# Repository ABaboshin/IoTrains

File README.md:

# IoTrains

Internet of Trains :)

The existing systems in the market are either with old roots (DCC) or not opensource (Märklin). More then that they were built over 20 years ago and therefore have historical restrictions. In order to be able more flexible I started to write a firmware for the trains and accessories using ESP32/ESP8266.

The projects consists of:
 - [Firmware](./firmware/) which is written in c++ using PlatformIO,
 - MQTT Broker, see [emqx](./emqx) as an example,
 - A [backend](./webui/server) written in typesript,
 - as well [frontend](./webui/client/) in react,
 - [json schema](./jsonschema/) describes a mqtt based protocol.

# License
The source code and schematic are licensed under MIT license.

The train's STL files are licensed under CC BY-NC-SA 4.0.

# Notes
 - Connect an audio amplifier to an i2s capable pin i.e. DAC_1.

## TODO
 - multiple rfid
 - responsive ui / refresh on update
 - process rfid events
 - sqlite3
 - main board max 4 x 2.3 c

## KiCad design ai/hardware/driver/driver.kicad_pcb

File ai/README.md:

# IoTrains train controller hardware (AI-generated)

Two 23 x 40 mm, 2-layer KiCad 10 boards for controlling a model train from an ESP32, joined by a 10-wire cable.

**Status:** schematics and PCBs are complete and fully routed, but nothing has been built or reviewed by a person. Routing is autorouted (Freerouting) except the buck converter, which is laid out by hand. Review both boards in KiCad before ordering.

| Board | Project | Contents |
|---|---|---|
| MCU | [hardware/mcu/mcu.kicad_pro](hardware/mcu/mcu.kicad_pro) | ESP32-S3-MINI-1-N8, MAX98357A I2S amplifier, BOOT and RESET buttons |
| Driver | [hardware/driver/driver.kicad_pro](hardware/driver/driver.kicad_pro) | Bridge rectifier, 3.3 V buck converter, BDR6133 motor driver, TLC5940 LED driver |

All parts are on the top side. Connector labels are on the bottom silkscreen. There are no mounting holes.

Every connector sits on a short edge, so all cables leave along the length of the board:

| Board | Top edge | Bottom edge (left to right) |
|---|---|---|
| MCU | Antenna, no connectors | `LINK`, `USB`, `SPK` |
| Driver | `LINK`, `3V3` | `12V`, `LED`, `MOTOR` |

## Requirements and how they are met

| Requirement | Result |
|---|---|
| Max 23 x 40 mm, up to 3 boards | 2 boards, each 23 x 40 mm |
| ESP32, module or bare chip, whichever is cheaper | ESP32-S3-MINI-1-N8 module (see below) |
| S2B-ZR and SM10B-SRSS-TB connectors | Used for every connector |
| Cables must run parallel to the long side | Every connector is on a short edge |
| 12 V DC input, unknown polarity | ABS210 bridge rectifier on the input |
| USB pins on an S2B connector | `USB` on the MCU board (IO19/IO20) |
| One BDR6133 motor driver, outputs exposed | On the driver board, `MOTOR` connector |
| 6 LED outputs, TLC5940 allowed | TLC5940 with 8 outputs on the `LED` connector |
| Audio chip with speaker output, otherwise expose I2S | MAX98357A with `SPK` connector; I2S is not exposed |

**Module vs bare chip:** at JLCPCB on 2026-11-27 the module was $4.72 and the bare ESP32-S3FN8 $3.27. The $1.45 difference does not cover a crystal, RF matching parts and an antenna that needs tuning, so the module is used.

## Connectors

### MCU board

| Connector | Type | Pins |
|---|---|---|
| `LINK` (J1) | SM10B | See link pinout below |
| `USB` (J2) | S2B | 1 = D+ (IO20), 2 = D- (IO19) |
| `SPK` (J4) | S2B | 1 = SPK+, 2 = SPK- |

The MCU board has no power connector of its own. It gets 3.3 V over `LINK` pin 2.

### Driver board

| Connector | Type | Pins |
|---|---|---|
| `12V` (J1) | S2B | 12 V DC, either polarity |
| `MOTOR` (J2) | S2B | 1 = OUTA, 2 = OUTB |
| `LINK` (J3) | SM10B | See link pinout below |
| `LED` (J4) | SM10B | 1 and 10 = LED anodes (bridge output, about 10 V), 2-9 = OUT0-OUT7 |
| `3V3` (J5) | S2B | 1 = GND, 2 = +3V3 |

### Link cable

The cable must be wired 1:1 (pin n to pin n).

| Pin | Signal | ESP32 pin | Driver board |
|---|---|---|---|
| 1 | GND | | |
| 2 | +3V3 | | From the buck converter |
| 3 | GSCLK | IO11 | TLC5940 |
| 4 | BLANK | IO12 | TLC5940, 10k pull-up |
| 5 | SIN | IO13 | TLC5940 |
| 6 | SCLK | IO14 | TLC5940 |
| 7 | XLAT | IO15 | TLC5940 |
| 8 | VPRG | IO16 | TLC5940, 10k pull-down |
| 9 | MOT_A | IO17 | BDR6133 INA, 100k pull-down |
| 10 | MOT_B | IO18 | BDR6133 INB, 100k pull-down |

The TLC5940 pins match the mapping in the comment in `firmware/basic_train/src/main.cpp`.

## Circuit notes

### Power

- The 12 V input goes through the ABS210 bridge, so polarity does not matter. The bridge output (`VM`, about 10 V) feeds the motor driver, the LED anodes and the buck converter.
- A TPS629210 makes 3.3 V. It is configured the same way as the existing `hardware/tps6292` board: 249k on VSET (3.3 V) and 52.3k on S-CONF (2.5 MHz, forced PWM, output discharge off).
- Keep the input at 16 V or below. The buck converter and the TLC5940 outputs are rated to 17 V.
- The S2B connectors are rated 1 A, which limits motor current.
- The `3V3` connector on the driver board is for powering both boards without 12 V, for example from a USB adapter while flashing. Do not feed 3.3 V into it while 12 V is connected.

### Motor

- BDR6133 logic: INA high / INB low = forward, INA low / INB high = reverse, both high = brake, both low = stop.
- The pull-downs keep the motor off while the ESP32 boots.

### LEDs

- Each output is a constant-current sink of 8.3 mA (39.06 / 4.7k), so LEDs need no series resistors. Connect each LED between an anode pin and an output pin.
- BLANK is pulled high so the LEDs stay off until the firmware runs.
- DCPRG is tied to 3.3 V, as on the existing `hardware/tlc5940` board. The dot-correction register is undefined after power-up, so the firmware must write it (with VPRG high) before using the outputs.
- OUT8-OUT15 are not connected.

### Audio

| Signal | ESP32 pin |
|---|---|
| I2S DIN | IO47 |
| I2S BCLK | IO33 |
| I2S LRCLK | IO34 |
| Amplifier SD_MODE | IO21, 510k pull-up to 3.3 V |

- With IO21 floating, the amplifier plays (L+R)/2. Driving IO21 low shuts it down; driving it high selects the left channel only.
- Gain is fixed at 9 dB.
- The amplifier runs from 3.3 V. Expect roughly 0.6 W into 8 ohm; this is extrapolated from the datasheet's 0.77 W at 3.7 V.
- Use a 4-8 ohm speaker. The output is bridge-tied, so neither speaker wire may be connected to GND.
- The existing firmware does not drive these pins yet (the I2S code in `MP3Player.cpp` is commented out).

### ESP32

- BOOT button on IO0 (left of the module), RESET button on EN (right of the module).
- No copper is placed under the module's antenna (top 5.3 mm of the board).

## Bill of materials

Every part carries an `LCSC` field in the schematic and on the PCB footprint.

### MCU board

| Ref | Part | Package | LCSC |
|---|---|---|---|
| U1 | ESP32-S3-MINI-1-N8 | Module | C2913206 |
| U2 | MAX98357AETE+T | TQFN-16 | C910544 |
| SW1, SW2 | TS-1088 tactile switch | SMD | C720477 |
| R1 | 10k | 0402 | C25744 |
| R2 | 510k | 0402 | C11616 |
| C1, C4 | 10 uF | 0603 | C19702 |
| C2, C5 | 100 nF | 0402 | C1525 |
| C3 | 1 uF | 0402 | C52923 |
| J1 | SM10B-SRSS-TB | | C160409 |
| J2, J4 | S2B-ZR | | C157930 |

### Driver board

| Ref | Part | Package | LCSC |
|---|---|---|---|
| D1 | ABS210 bridge | ABS | C84159 |
| U1 | TPS629210DRLR | SOT-583 | C5219301 |
| U2 | BDR6133 | ESOP-8 | C2687793 |
| U3 | TLC5940PWPR | HTSSOP-28 | C181653 |
| L1 | 2.2 uH, 3.3 A | 1210 | C6021483 |
| C1, C2 | 10 uF 25 V | 0805 | C15850 |
| C3 | 22 uF | 0805 | C45783 |
| C4, C5 | 100 nF | 0402 | C1525 |
| R1 | 249k | 0603 | C22918 |
| R2 | 52.3k | 0603 | C23198 |
| R3, R4 | 100k | 0402 | C25741 |
| R5 | 4.7k | 0402 | C25900 |
| R6, R7 | 10k | 0402 | C25744 |
| J1, J2, J5 | S2B-ZR | | C157930 |
| J3, J4 | SM10B-SRSS-TB | | C160409 |

## Verification

Checked with `kicad-cli` (KiCad 10.0.1):

| Board | ERC | DRC | Unconnected | Schematic parity |
|---|---|---|---|---|
| MCU | 1 warning | 1 error, 10 warnings | 0 | OK |
| Driver | 0 | 8 warnings | 0 | OK |

- The MCU ERC warning is a pin-type mismatch on the exposed pad of the stock MAX98357A symbol.
- The MCU DRC error is a courtyard overlap between `USB` (J2) and `SPK` (J4). It is expected: the three connectors only fit on the 23 mm edge with their bodies about 0.2 mm apart.
- All DRC warnings are silkscreen overlaps between neighbouring connectors, for the same reason.
- IC pinouts were checked against the datasheets for the BDR6133, TPS629210, TLC5940 and MAX98357A.
- Design rules: 0.2 mm tracks (0.3-0.6 mm for power, motor and speaker), 0.15 mm clearance, 0.6 / 0.3 mm vias, 0.3 mm copper-to-edge.

## Before ordering

- **TLC5940PWPR (C181653):** JLCPCB showed 1 in stock on 2026-11-27, so it would be a pre-order.
- **ESP32 module:** JLCPCB lists it as "Standard PCBA only", not Economic.
- **100 nF capacitor (C1525):** LCSC's own site showed 0 stock on 2026-11-27. JLCPCB's assembly stock for it was not checked.
- **Production files:** gerbers, BOM and placement files have not been generated. Use the Fabrication Toolkit plugin as on the other boards in `hardware/`.
- **Connector spacing:** neighbouring connectors are 0.2-0.25 mm apart, and the outer ones on the bottom edges are 0.2-0.25 mm from the board edge. Check this against real parts before ordering in quantity.
- **LED tracks:** on the driver board the eight LED tracks run under the body of the bridge rectifier, between its pads.
- **Review:** look over the autorouted tracks, especially the motor and power paths.

## Regenerating the design

The KiCad files are generated from [hardware/tools/design.py](hardware/tools/design.py), which holds the parts, nets and placement for both boards.

```
python ai/hardware/tools/build.py            # both boards
python ai/hardware/tools/build.py driver     # one board
```

This rewrites the schematic and PCB, re-runs the autorouter and prints the ERC/DRC summary. Manual edits made in KiCad are lost, and the routing differs on every run.

It needs:

- KiCad 10 in `C:\Program Files\KiCad\10.0`
- Java 21 and `freerouting-1.9.0.jar` in `%TEMP%` (from the Freerouting GitHub releases; 2.1.0 failed to route these boards)
- The JST footprint libraries `LIB_S2B-ZR_LF__SN_` and `LIB_SM10B-SRSS-TB_LF__SN_` in KiCad's global footprint table
- `hardware/esp32/esp32.kicad_pro` in this repo, used as the project template

| File | Purpose |
|---|---|
| `design.py` | Parts, nets, schematic and PCB positions, hand-routed tracks |
| `gen_sch.py` | Writes the schematic, project file and library tables |
| `gen_pcb.py` | Places footprints, autoroutes, adds ground pours and labels |
| `check.py` | Runs ERC and DRC and prints a summary |
| `build.py` | Runs the three steps above |
| `build_lib.py` | Rebuilds `hardware/lib` from symbols and footprints in the repo's existing boards |
| `sexp.py`, `symlib.py`, `netlist.py` | Helpers for KiCad file formats |

The shared symbols and footprints are in [hardware/lib](hardware/lib).

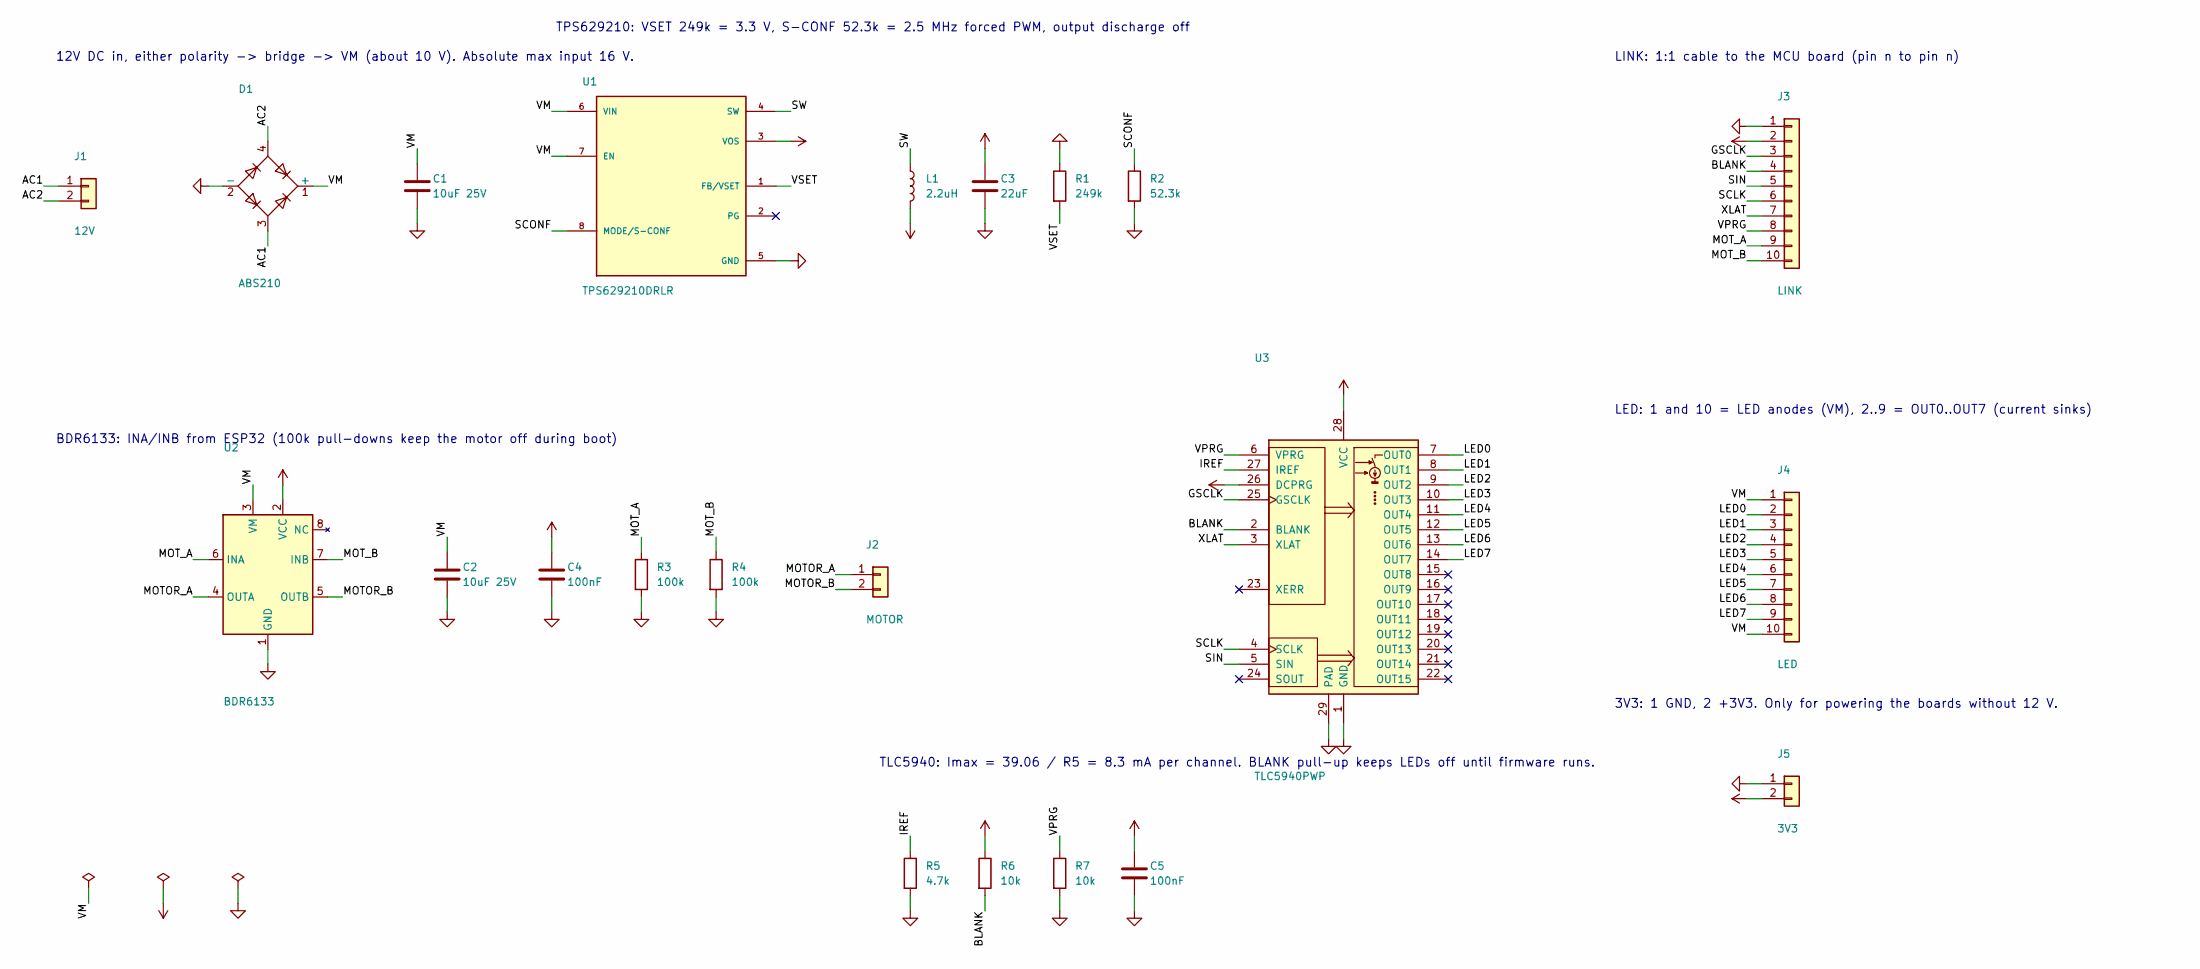
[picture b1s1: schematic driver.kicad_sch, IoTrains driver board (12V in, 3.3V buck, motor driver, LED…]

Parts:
C1, C2: 10uF 25V; C_0805_2012Metric; LCSC C15850
C3: 22uF; C_0805_2012Metric; LCSC C45783
C4, C5: 100nF; C_0402_1005Metric; LCSC C1525
D1: ABS210; Diode_Bridge_Diotec_ABS; LCSC C84159
J1: 12V; S2BZRLFSN; LCSC C157930
J2: MOTOR; S2BZRLFSN; LCSC C157930
J3: LINK; SM10B-SRSS-TB; LCSC C160409
J4: LED; SM10B-SRSS-TB; LCSC C160409
J5: 3V3; S2BZRLFSN; LCSC C157930
L1: 2.2uH; L_1210_3225Metric; LCSC C6021483
R1: 249k; R_0603_1608Metric; LCSC C22918
R2: 52.3k; R_0603_1608Metric; LCSC C23198
R3, R4: 100k; R_0402_1005Metric; LCSC C25741
R5: 4.7k; R_0402_1005Metric; LCSC C25900
R6, R7: 10k; R_0402_1005Metric; LCSC C25744
U1: TPS629210DRLR; SOT-583-8; LCSC C5219301
U2: BDR6133; SOIC-8-1EP_3.9x4.9mm_P1.27mm_EP2.41x3.3mm_ThermalVias; LCSC C2687793
U3: TLC5940PWP; HTSSOP-28-1EP_4.4x9.7mm_P0.65mm_EP3.4x9.5mm_Mask2.4x6.17mm_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; LCSC C181653

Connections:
+3V3: C3.1, C4.1, C5.1, J3.2, J5.2, L1.2, R6.1, U1.3 (VOS), U2.2 (VCC), U3.26 (DCPRG), U3.28 (VCC)
/AC1: D1.3, J1.1
/AC2: D1.4, J1.2
/BLANK: J3.4, R6.2, U3.2 (BLANK)
/GSCLK: J3.3, U3.25 (GSCLK)
/IREF: R5.1, U3.27 (IREF)
/LED0: J4.2, U3.7 (OUT0)
/LED1: J4.3, U3.8 (OUT1)
/LED2: J4.4, U3.9 (OUT2)
/LED3: J4.5, U3.10 (OUT3)
/LED4: J4.6, U3.11 (OUT4)
/LED5: J4.7, U3.12 (OUT5)
/LED6: J4.8, U3.13 (OUT6)
/LED7: J4.9, U3.14 (OUT7)
/MOTOR_A: J2.1, U2.4 (OUTA)
/MOTOR_B: J2.2, U2.5 (OUTB)
/MOT_A: J3.9, R3.1, U2.6 (INA)
/MOT_B: J3.10, R4.1, U2.7 (INB)
/SCLK: J3.6, U3.4 (SCLK)
/SCONF: R2.1, U1.8 (MODE/S-CONF)
/SIN: J3.5, U3.5 (SIN)
/SW: L1.1, U1.4 (SW)
/VM: C1.1, C2.1, D1.1 (+), J4.1, J4.10, U1.6 (VIN), U1.7 (EN), U2.3 (VM)
/VPRG: J3.8, R7.1, U3.6 (VPRG)
/VSET: R1.2, U1.1 (FB/VSET)
/XLAT: J3.7, U3.3 (XLAT)
GND: C1.2, C2.2, C3.2, C4.2, C5.2, D1.2 (-), J3.1, J5.1, R1.1, R2.2, R3.2, R4.2, R5.2, R7.2, U1.5 (GND), U2.1 (GND), U2.9 (GND), U3.1 (GND), U3.29 (PAD)

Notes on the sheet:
12V DC in, either polarity -> bridge -> VM (about 10 V). Absolute max input 16 V.
LED: 1 and 10 = LED anodes (VM), 2..9 = OUT0..OUT7 (current sinks)
LINK: 1:1 cable to the MCU board (pin n to pin n)
3V3: 1 GND, 2 +3V3. Only for powering the boards without 12 V.
BDR6133: INA/INB from ESP32 (100k pull-downs keep the motor off during boot)
TPS629210: VSET 249k = 3.3 V, S-CONF 52.3k = 2.5 MHz forced PWM, output discharge off
TLC5940: Imax = 39.06 / R5 = 8.3 mA per channel. BLANK pull-up keeps LEDs off until firmware runs.

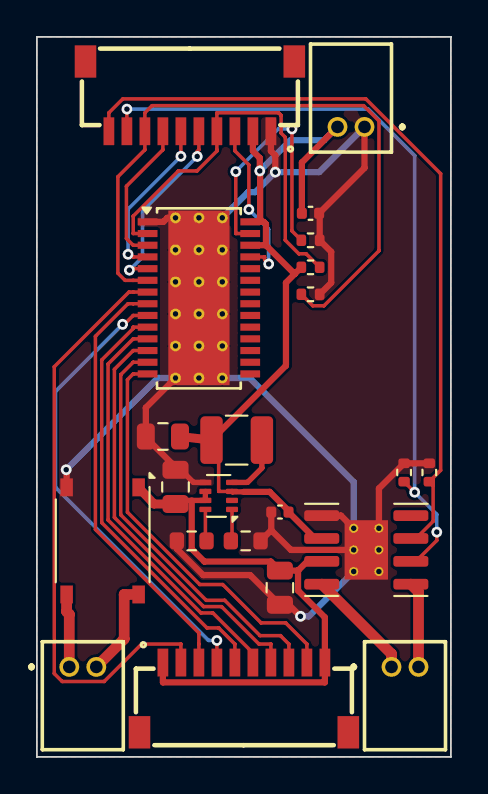
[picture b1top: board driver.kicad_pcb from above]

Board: 2 copper layers, 23.0 x 40.0 mm, 22 parts (0 on the bottom side), 27 nets.

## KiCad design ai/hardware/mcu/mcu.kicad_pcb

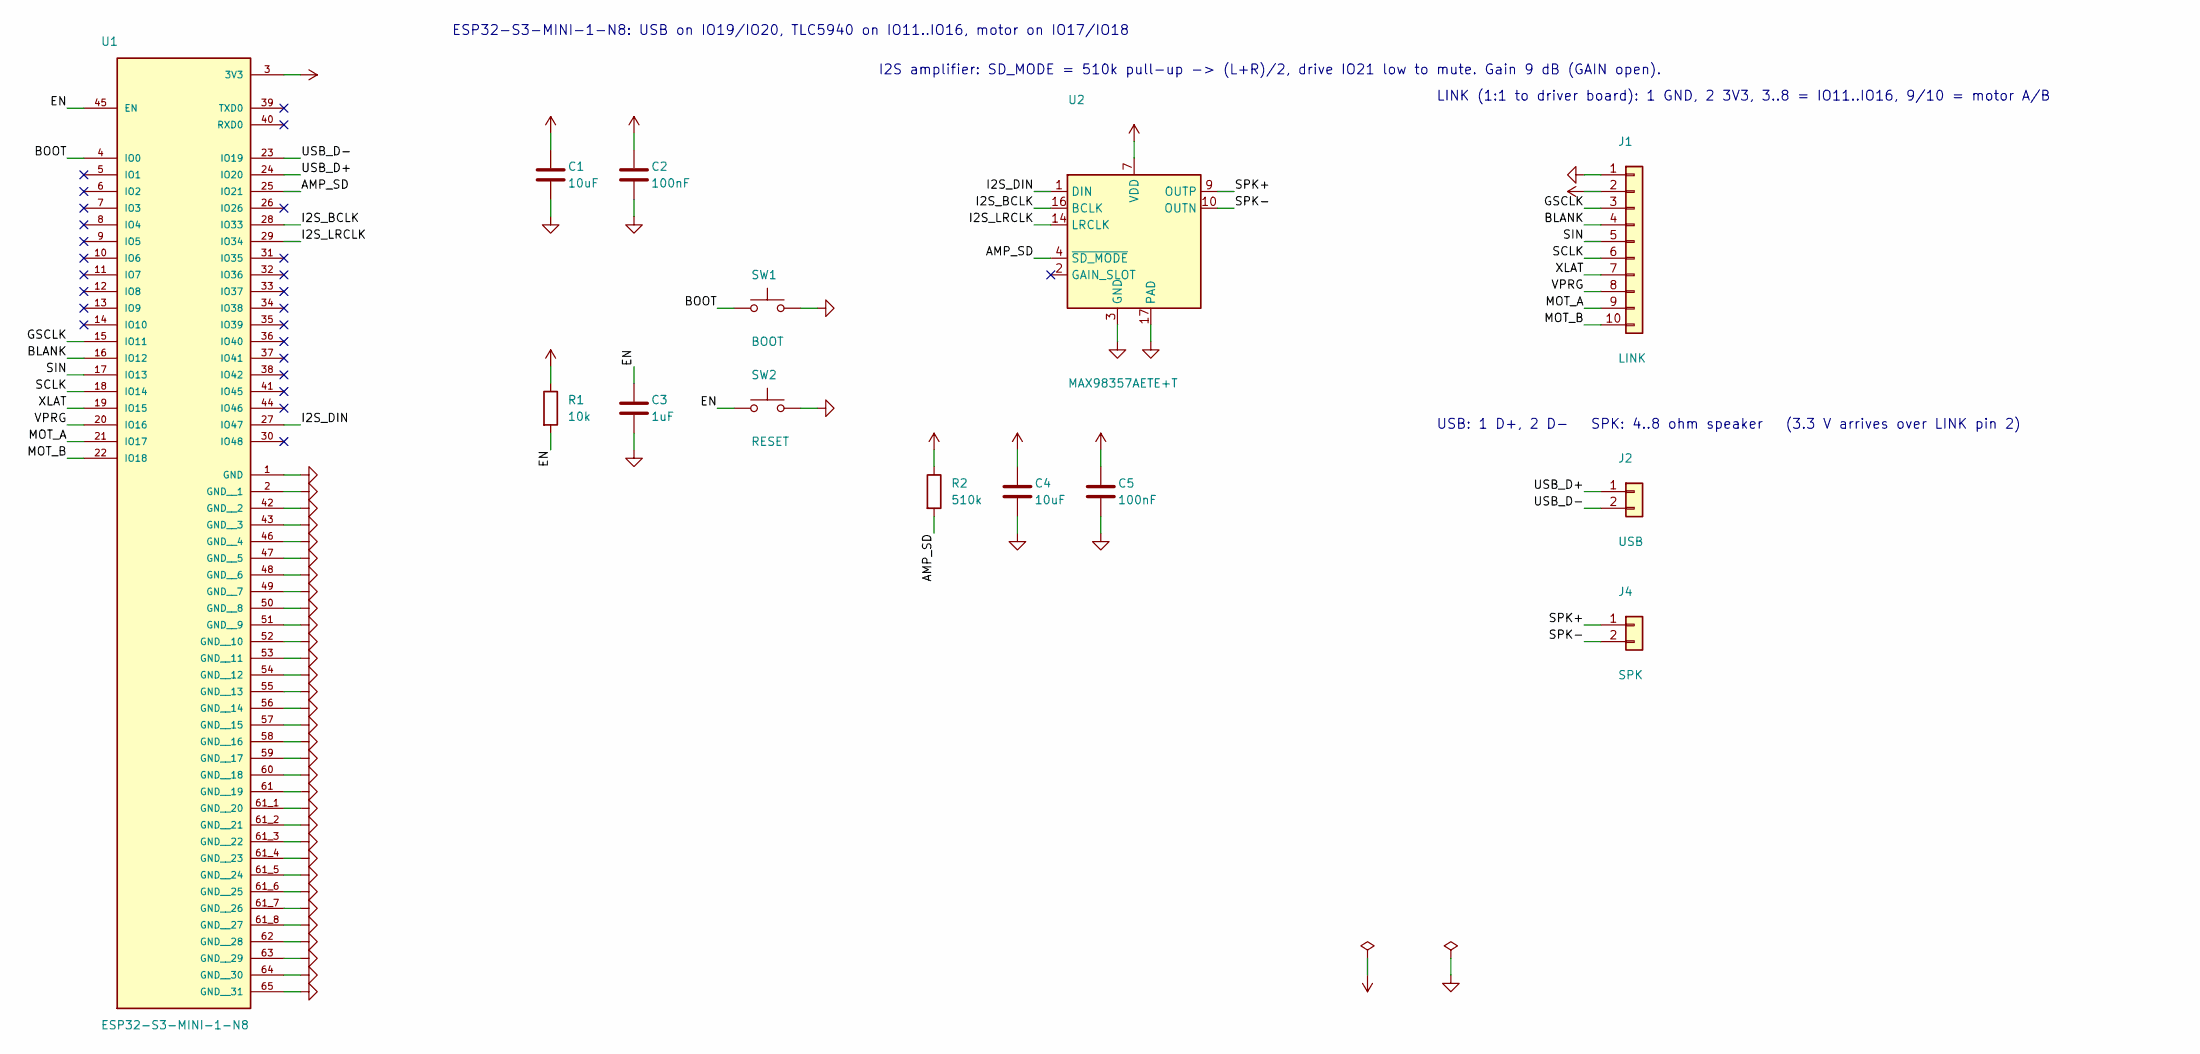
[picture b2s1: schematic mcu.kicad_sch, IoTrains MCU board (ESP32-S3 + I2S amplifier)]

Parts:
C1, C4: 10uF; C_0603_1608Metric; LCSC C19702
C2, C5: 100nF; C_0402_1005Metric; LCSC C1525
C3: 1uF; C_0402_1005Metric; LCSC C52923
J1: LINK; SM10B-SRSS-TB; LCSC C160409
J2: USB; S2BZRLFSN; LCSC C157930
J4: SPK; S2BZRLFSN; LCSC C157930
R1: 10k; R_0402_1005Metric; LCSC C25744
R2: 510k; R_0402_1005Metric; LCSC C11616
SW1: BOOT; SW_SPST_TS-1088-xR020; LCSC C720477
SW2: RESET; SW_SPST_TS-1088-xR020; LCSC C720477
U1: ESP32-S3-MINI-1-N8; XCVR_ESP32-S3-MINI-1-N8; LCSC C2913206
U2: MAX98357AETE+T; TQFN-16-1EP_3x3mm_P0.5mm_EP1.23x1.23mm; LCSC C910544

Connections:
+3V3: C1.1, C2.1, C4.1, C5.1, J1.2, R1.1, R2.1, U1.3 (3V3), U2.7 (VDD), U2.8 (VDD)
/AMP_SD: R2.2, U1.25 (IO21), U2.4 (~SD_MODE)
/BLANK: J1.4, U1.16 (IO12)
/BOOT: SW1.1, U1.4 (IO0)
/EN: C3.1, R1.2, SW2.1, U1.45 (EN)
/GSCLK: J1.3, U1.15 (IO11)
/I2S_BCLK: U1.28 (IO33), U2.16 (BCLK)
/I2S_DIN: U1.27 (IO47), U2.1 (DIN)
/I2S_LRCLK: U1.29 (IO34), U2.14 (LRCLK)
/MOT_A: J1.9, U1.21 (IO17)
/MOT_B: J1.10, U1.22 (IO18)
/SCLK: J1.6, U1.18 (IO14)
/SIN: J1.5, U1.17 (IO13)
/SPK+: J4.1, U2.9 (OUTP)
/SPK-: J4.2, U2.10 (OUTN)
/USB_D+: J2.1, U1.24 (IO20)
/USB_D-: J2.2, U1.23 (IO19)
/VPRG: J1.8, U1.20 (IO16)
/XLAT: J1.7, U1.19 (IO15)
GND: C1.2, C2.2, C3.2, C4.2, C5.2, J1.1, SW1.2, SW2.2, U1.1 (GND), U1.2 (GND__1), U1.42 (GND__2), U1.43 (GND__3), U1.46 (GND__4), U1.47 (GND__5), U1.48 (GND__6), U1.49 (GND__7), U1.50 (GND__8), U1.51 (GND__9), U1.52 (GND__10), U1.53 (GND__11), U1.54 (GND__12), U1.55 (GND__13), U1.56 (GND__14), U1.57 (GND__15), U1.58 (GND__16), U1.59 (GND__17), U1.60 (GND__18), U1.61 (GND__19), U1.61_1 (GND__20), U1.61_2 (GND__21), U1.61_3 (GND__22), U1.61_4 (GND__23), U1.61_5 (GND__24), U1.61_6 (GND__25), U1.61_7 (GND__26), U1.61_8 (GND__27), U1.62 (GND__28), U1.63 (GND__29), U1.64 (GND__30), U1.65 (GND__31), U2.3 (GND), U2.11 (GND), U2.15 (GND), U2.17 (PAD)

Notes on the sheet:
USB: 1 D+, 2 D- SPK: 4..8 ohm speaker (3.3 V arrives over LINK pin 2)
I2S amplifier: SD_MODE = 510k pull-up -> (L+R)/2, drive IO21 low to mute. Gain 9 dB (GAIN open).
ESP32-S3-MINI-1-N8: USB on IO19/IO20, TLC5940 on IO11..IO16, motor on IO17/IO18
LINK (1:1 to driver board): 1 GND, 2 3V3, 3..8 = IO11..IO16, 9/10 = motor A/B

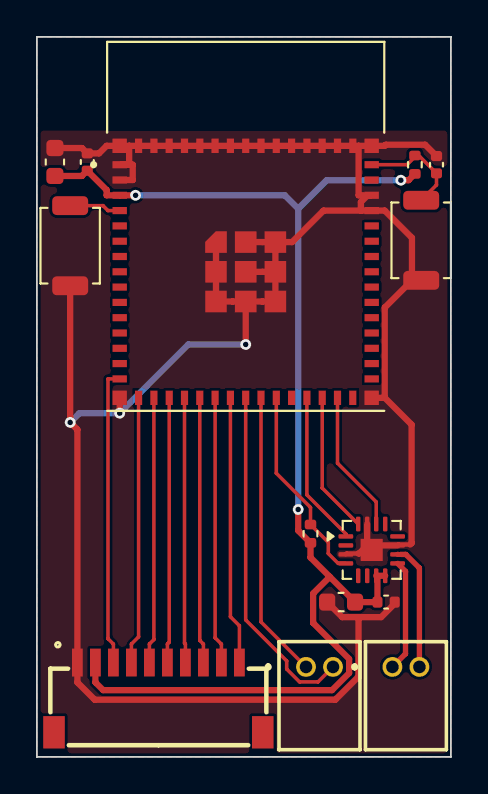
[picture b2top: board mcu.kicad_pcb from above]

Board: 2 copper layers, 23.0 x 40.0 mm, 14 parts (0 on the bottom side), 20 nets.

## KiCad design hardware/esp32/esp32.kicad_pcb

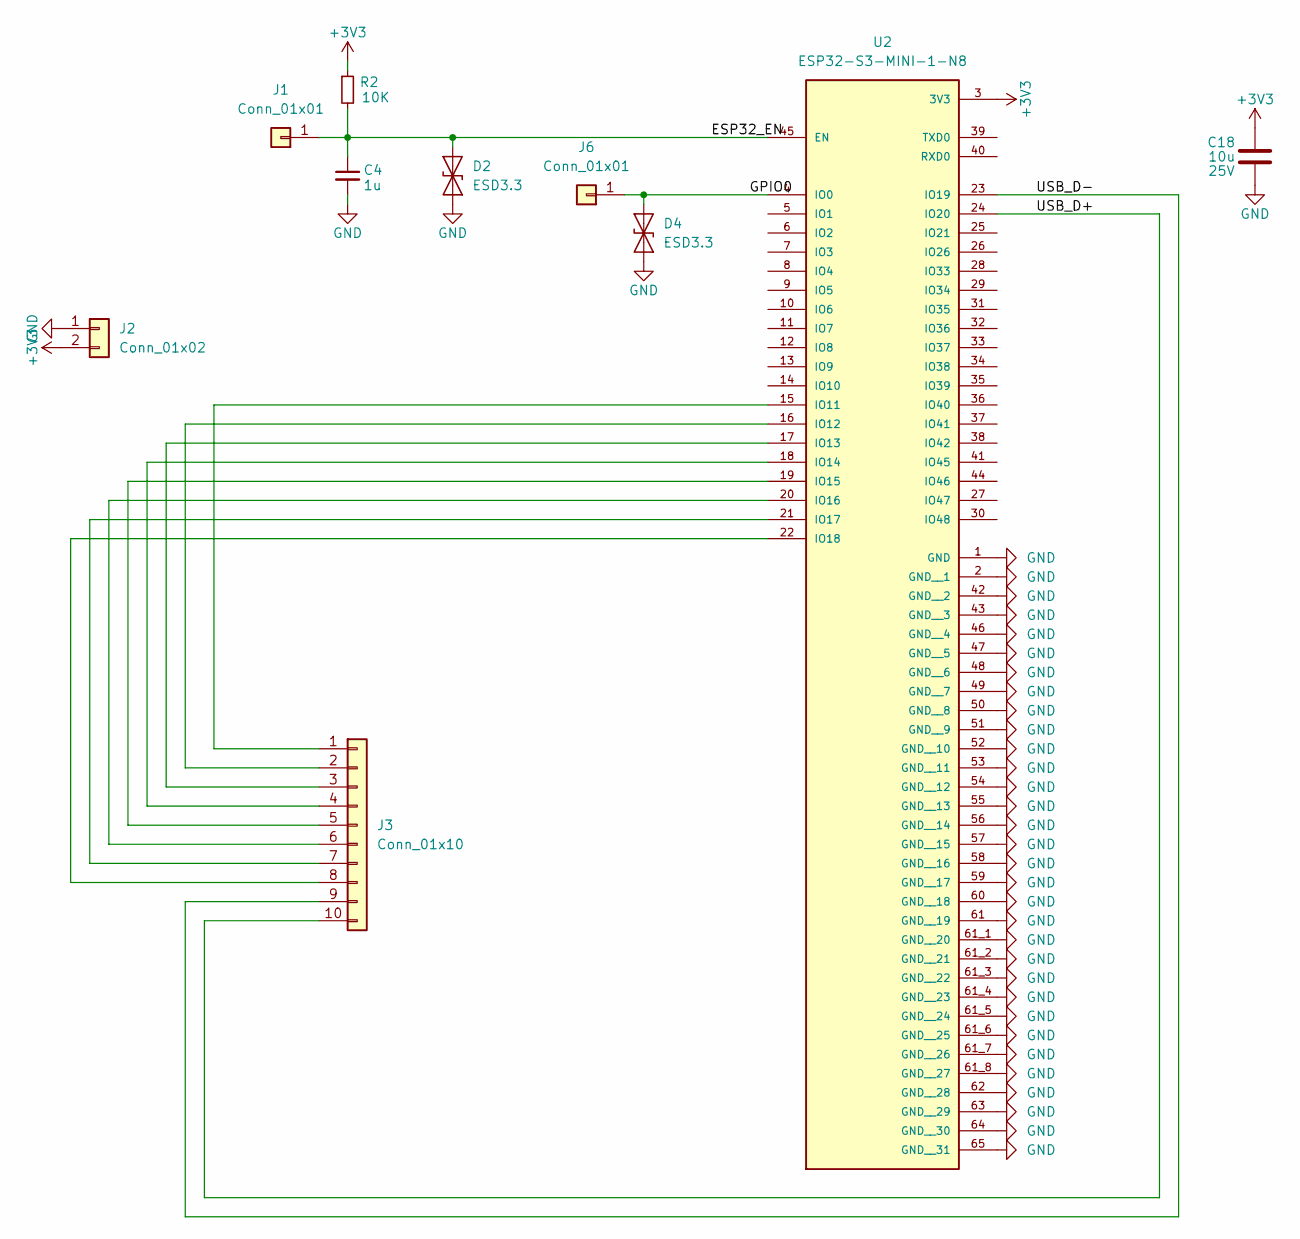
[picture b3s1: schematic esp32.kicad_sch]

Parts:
C4: 1u; C_0603_1608Metric
C18: 10u; C_0603_1608Metric; Voltage 25V; LCSC Part # C96446
D2, D4: ESD3.3; SOT-723
J1, J6: Conn_01x01; PinHeader_1x01_P1.00mm_Vertical
J2: Conn_01x02; S2BZRLFSN; LCSC C157930
J3: Conn_01x10; SM10B-SRSS-TB; LCSC C160409
R2: 10K; R_0402_1005Metric
U2: ESP32-S3-MINI-1-N8; XCVR_ESP32-S3-MINI-1-N8; PARTREV v0.6

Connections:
+3V3: C18.1, J2.2, R2.1, U2.3 (3V3)
/ESP32_EN: C4.1, D2.2 (A2), J1.1, R2.2, U2.45 (EN)
/GPIO0: D4.2 (A2), J6.1, U2.4 (IO0)
/USB_D+: J3.10, U2.24 (IO20)
/USB_D-: J3.9, U2.23 (IO19)
GND: C4.2, C18.2, D2.1 (A1), D4.1 (A1), J2.1, U2.1 (GND), U2.2 (GND__1), U2.42 (GND__2), U2.43 (GND__3), U2.46 (GND__4), U2.47 (GND__5), U2.48 (GND__6), U2.49 (GND__7), U2.50 (GND__8), U2.51 (GND__9), U2.52 (GND__10), U2.53 (GND__11), U2.54 (GND__12), U2.55 (GND__13), U2.56 (GND__14), U2.57 (GND__15), U2.58 (GND__16), U2.59 (GND__17), U2.60 (GND__18), U2.61 (GND__19), U2.61_1 (GND__20), U2.61_2 (GND__21), U2.61_3 (GND__22), U2.61_4 (GND__23), U2.61_5 (GND__24), U2.61_6 (GND__25), U2.61_7 (GND__26), U2.61_8 (GND__27), U2.62 (GND__28), U2.63 (GND__29), U2.64 (GND__30), U2.65 (GND__31)
unnamed: J3.1, U2.15 (IO11)
unnamed: J3.2, U2.16 (IO12)
unnamed: J3.3, U2.17 (IO13)
unnamed: J3.4, U2.18 (IO14)
unnamed: J3.5, U2.19 (IO15)
unnamed: J3.6, U2.20 (IO16)
unnamed: J3.7, U2.21 (IO17)
unnamed: J3.8, U2.22 (IO18)

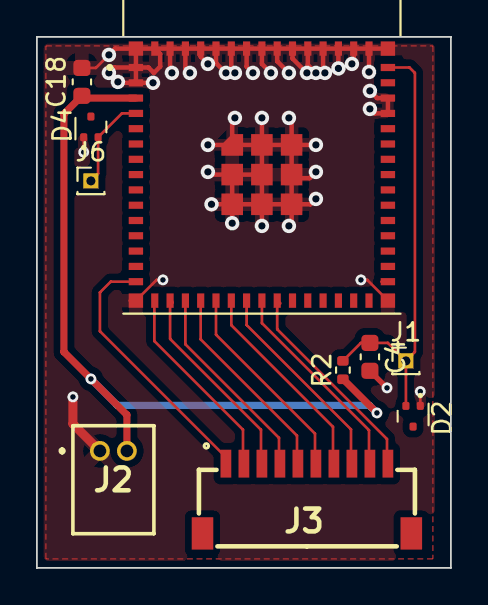
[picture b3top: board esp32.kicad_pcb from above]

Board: 2 copper layers, 23.0 x 29.5 mm, 10 parts (0 on the bottom side), 14 nets.

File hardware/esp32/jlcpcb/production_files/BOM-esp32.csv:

Comment,Designator,Footprint,LCSC,Quantity
10K,R2,R_0402_1005Metric,C25744,1
10u,C18,C_0603_1608Metric,C96446,1
1u,C4,C_0603_1608Metric,C15849,1
Conn_01x02,J2,S2BZRLFSN,C157930,1
Conn_01x10,J3,SM10B-SRSS-TB,C160409,1
ESD3.3,"D2,D4",SOT-723,C233435,2
ESP32-S3-MINI-1-N8,U2,XCVR_ESP32-S3-MINI-1-N8,C2913206,1
Conn_01x01,J1,PinHeader_1x01_P1.00mm_Vertical,,1
Conn_01x01,J6,PinHeader_1x01_P1.00mm_Vertical,,1

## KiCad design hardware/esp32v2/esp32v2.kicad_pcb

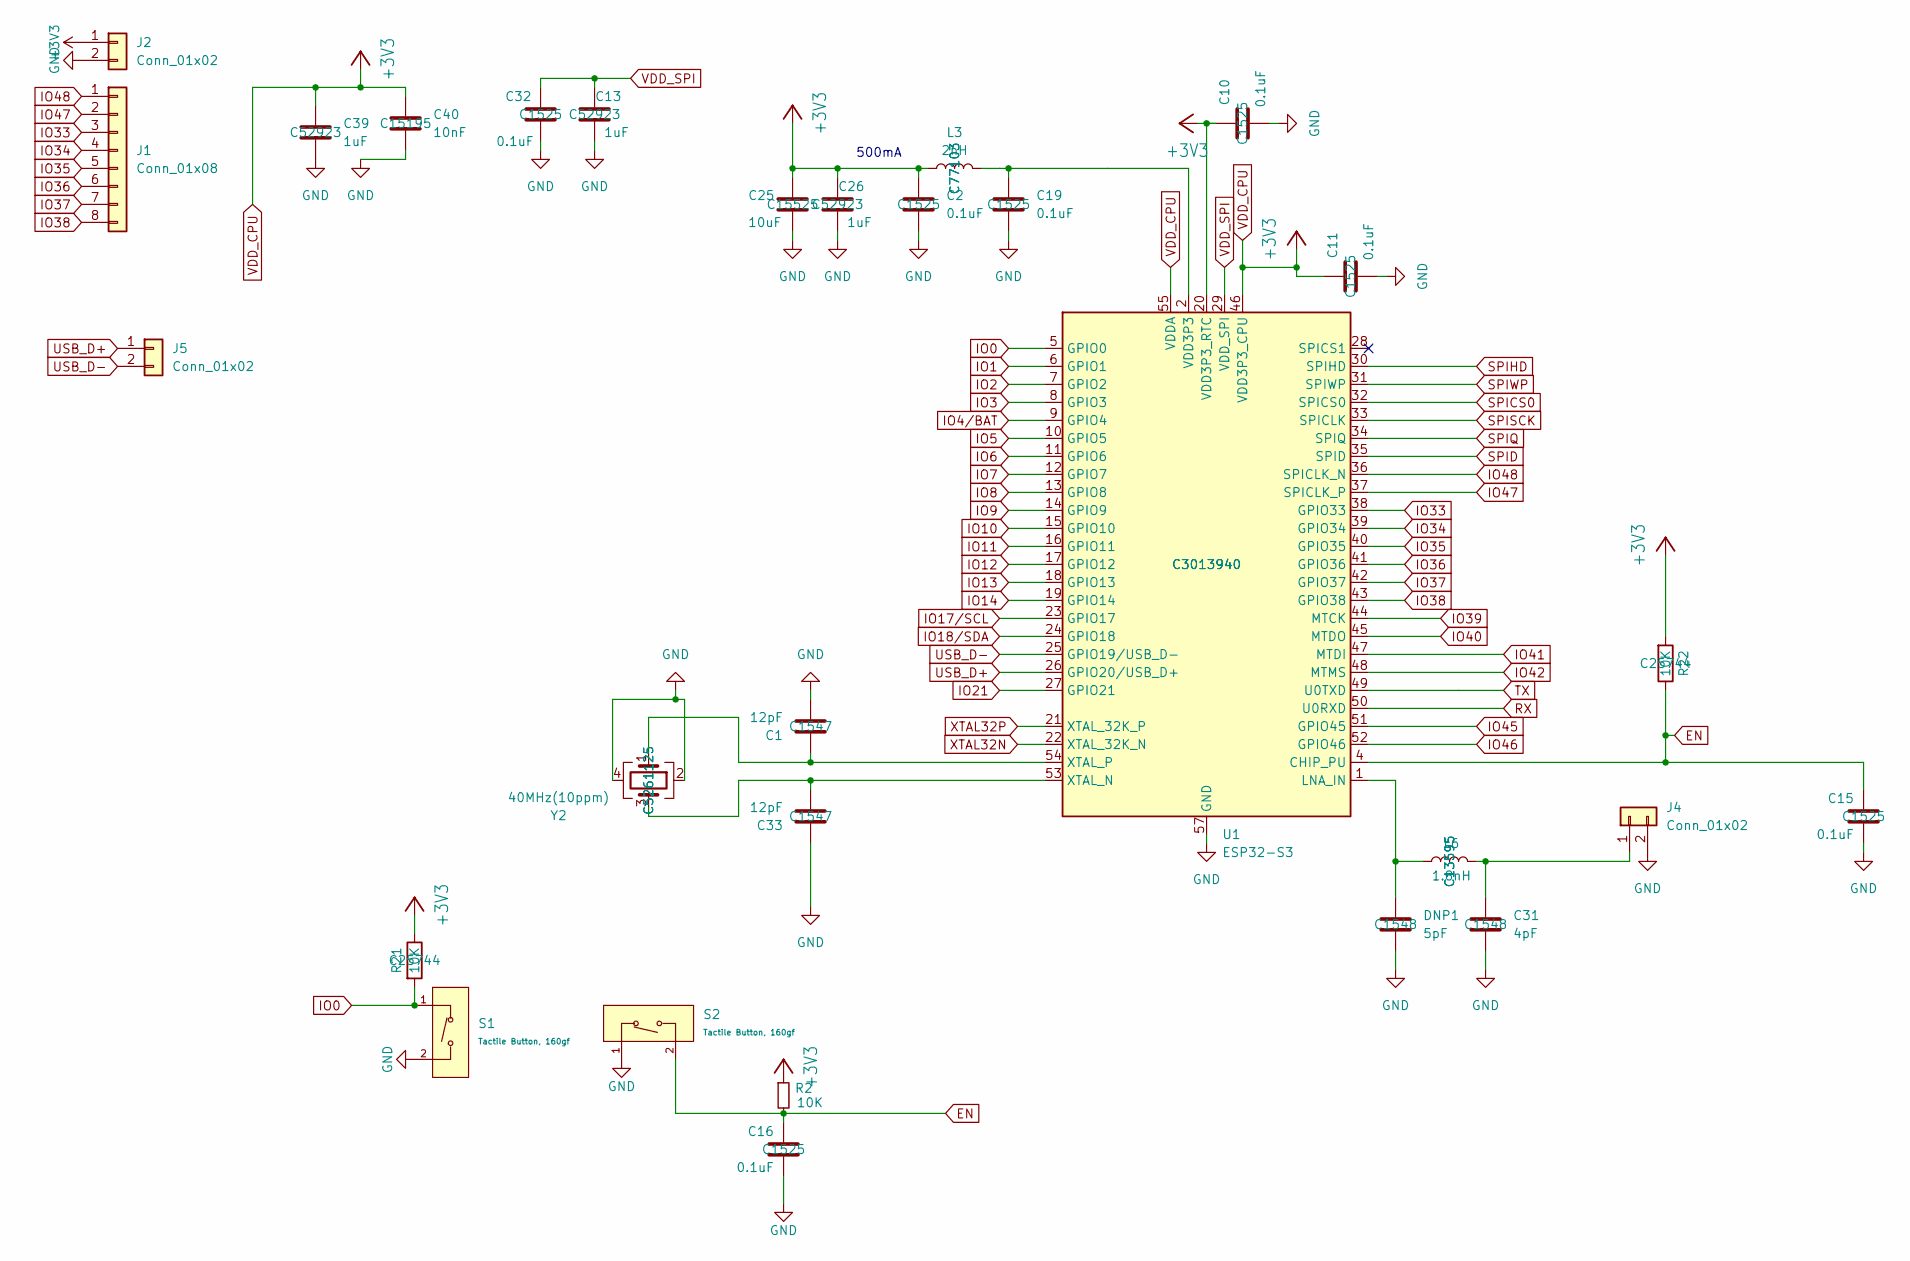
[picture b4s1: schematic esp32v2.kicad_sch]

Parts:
C1, C33: 12pF; C_0201_0603Metric; MNF PART NUMBER C1547; LCSC C1547
C2, C10, C11, C15, C16, C19, C32: 0.1uF; C_0201_0603Metric; MNF PART NUMBER C1525; LCSC C1525
C13, C26, C39: 1uF; C_0201_0603Metric; MNF PART NUMBER C52923; LCSC C52923
C25: 10uF; C_0201_0603Metric; MNF PART NUMBER C15525; LCSC C15525
C31: 4pF; C_0201_0603Metric; MNF PART NUMBER C1548; LCSC C1548
C40: 10nF; C_0201_0603Metric; MNF PART NUMBER C15195; LCSC C15195
DNP1: 5pF; C_0201_0603Metric; MNF PART NUMBER C1548; LCSC C1548
J1: Conn_01x08; JST_SHL_SM08B-SHLS-TF_1x08-1MP_P1.00mm_Horizontal
J2: Conn_01x02; S2BZRLFSN; LCSC C157930
J4: Conn_01x02; U.FL_Molex_MCRF_73412-0110_Vertical
J5: Conn_01x02; JST_SH_BM02B-SRSS-TB_1x02-1MP_P1.00mm_Vertical; LCSC C157930
L3: 2nH; L_0201_0603Metric; MNF PART NUMBER C77103; LCSC C77103
L6: 1.8nH; L_0201_0603Metric; MNF PART NUMBER C13595; LCSC C13595
R2: 10K; R_0201_0603Metric
R21, R22: 10K; R_0201_0603Metric; MNF PART NUMBER C25744; LCSC C25744
S1, S2: Tactile Button, 160gf; SW_TS-1088-AR02016; Voltage Rating (Dc) 12V; Part TS-1088-AR02016; LCSC C720477
U1: ESP32-S3; QFN-56-1EP_7x7mm_P0.4mm_EP4x4mm; MNF PART NUMBER C3013940; LCSC C3013940
Y2: 40MHz(10ppm); Crystal_SMD_2520-4Pin_2.5x2.0mm; MNF PART NUMBER C5261125; LCSC C5261125

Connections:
EN: C15.1, C16.1, R2.2, R22.1, S2.2 (B), U1.4 (CHIP_PU)
GND: C1.2, C2.2, C10.2, C11.2, C13.2, C15.2, C16.2, C19.2, C25.2, C26.2, C31.2, C32.2, C33.1, C39.2, C40.2, DNP1.2, J2.2, J4.2, S1.2 (B), S2.1 (A), U1.57 (GND), Y2.2, Y2.4
IO0: R21.2, S1.1 (A), U1.5 (GPIO0)
IO1: U1.6 (GPIO1)
IO2: U1.7 (GPIO2)
IO3: U1.8 (GPIO3)
IO4/BAT: U1.9 (GPIO4)
IO5: U1.10 (GPIO5)
IO6: U1.11 (GPIO6)
IO7: U1.12 (GPIO7)
IO8: U1.13 (GPIO8)
IO9: U1.14 (GPIO9)
IO10: U1.15 (GPIO10)
IO11: U1.16 (GPIO11)
IO12: U1.17 (GPIO12)
IO13: U1.18 (GPIO13)
IO14: U1.19 (GPIO14)
IO17/SCL: U1.23 (GPIO17)
IO18/SDA: U1.24 (GPIO18)
IO21: U1.27 (GPIO21)
IO33: J1.3, U1.38 (GPIO33)
IO34: J1.4, U1.39 (GPIO34)
IO35: J1.5, U1.40 (GPIO35)
IO36: J1.6, U1.41 (GPIO36)
IO37: J1.7, U1.42 (GPIO37)
IO38: J1.8, U1.43 (GPIO38)
IO39: U1.44 (MTCK)
IO40: U1.45 (MTDO)
IO41: U1.47 (MTDI)
IO42: U1.48 (MTMS)
IO45: U1.51 (GPIO45)
IO46: U1.52 (GPIO46)
IO47: J1.2, U1.37 (SPICLK_P)
IO48: J1.1, U1.36 (SPICLK_N)
unnamed: C19.1, L3.2, U1.2 (VDD3P3), U1.3 (VDD3P3)
unnamed: C31.1, J4.1, L6.2
unnamed: DNP1.1, L6.1, U1.1 (LNA_IN)
unnamed: C33.2, U1.53 (XTAL_N), Y2.3
unnamed: C1.1, U1.54 (XTAL_P), Y2.1
RX: U1.50 (U0RXD)
SPICS0: U1.32 (SPICS0)
SPID: U1.35 (SPID)
SPIHD: U1.30 (SPIHD)
SPIQ: U1.34 (SPIQ)
SPISCK: U1.33 (SPICLK)
SPIWP: U1.31 (SPIWP)
TX: U1.49 (U0TXD)
USB_D+: J5.1, U1.26 (GPIO20/USB_D+)
USB_D-: J5.2, U1.25 (GPIO19/USB_D-)
VDD_CPU: C2.1, C10.1, C11.1, C25.1, C26.1, C39.1, C40.1, J2.1, L3.1, R2.1, R21.1, R22.2, U1.20 (VDD3P3_RTC), U1.46 (VDD3P3_CPU), U1.55 (VDDA), U1.56 (VDDA)
VDD_SPI: C13.1, C32.1, U1.29 (VDD_SPI)
XTAL32N: U1.22 (XTAL_32K_N)
XTAL32P: U1.21 (XTAL_32K_P)

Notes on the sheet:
500mA

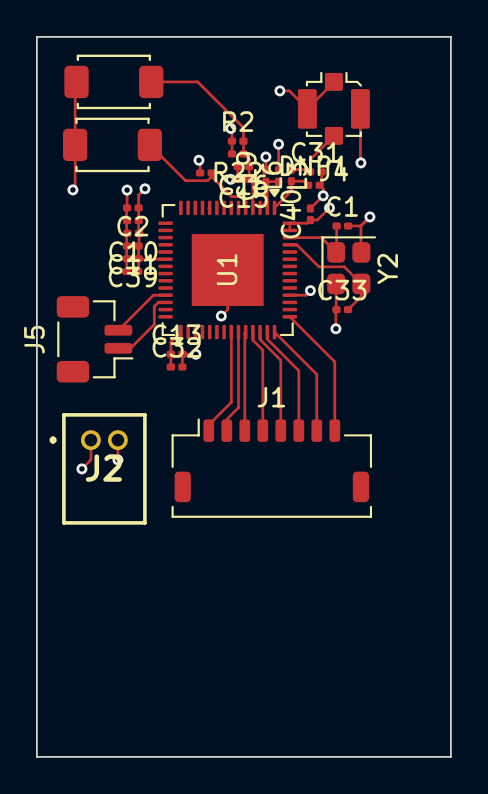
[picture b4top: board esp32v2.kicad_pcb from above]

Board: 4 copper layers, 23.0 x 40.0 mm, 29 parts (0 on the bottom side), 20 nets.

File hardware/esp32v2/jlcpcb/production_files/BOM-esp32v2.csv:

Comment,Designator,Footprint,LCSC,Quantity
0.1uF,"C10,C11,C15,C16,C19,C2,C32",C_0201_0603Metric,C1525,7
1.8nH,L6,L_0201_0603Metric,C13595,1
10K,"R21,R22",R_0201_0603Metric,C25744,2
10nF,C40,C_0201_0603Metric,C15195,1
10uF,C25,C_0201_0603Metric,C15525,1
12pF,"C1,C33",C_0201_0603Metric,C1547,2
1uF,"C13,C26,C39",C_0201_0603Metric,C52923,3
2nH,L3,L_0201_0603Metric,C77103,1
40MHz(10ppm),Y2,Crystal_SMD_2520-4Pin_2.5x2.0mm,C5261125,1
4pF,C31,C_0201_0603Metric,C1548,1
5pF,DNP1,C_0201_0603Metric,C1548,1
Conn_01x02,"J2,J5",S2BZRLFSN,C157930,2
ESP32-S3,U1,QFN-56-1EP_7x7mm_P0.4mm_EP4x4mm,C2913194,1
"Tactile Button, 160gf","S1,S2",SW_TS-1088-AR02016,C720477,2
10K,R2,R_0201_0603Metric,,1
Conn_01x08,J1,JST_SHL_SM08B-SHLS-TF_1x08-1MP_P1.00mm_Horizontal,,1
Conn_01x02,J4,U.FL_Molex_MCRF_73412-0110_Vertical,,1

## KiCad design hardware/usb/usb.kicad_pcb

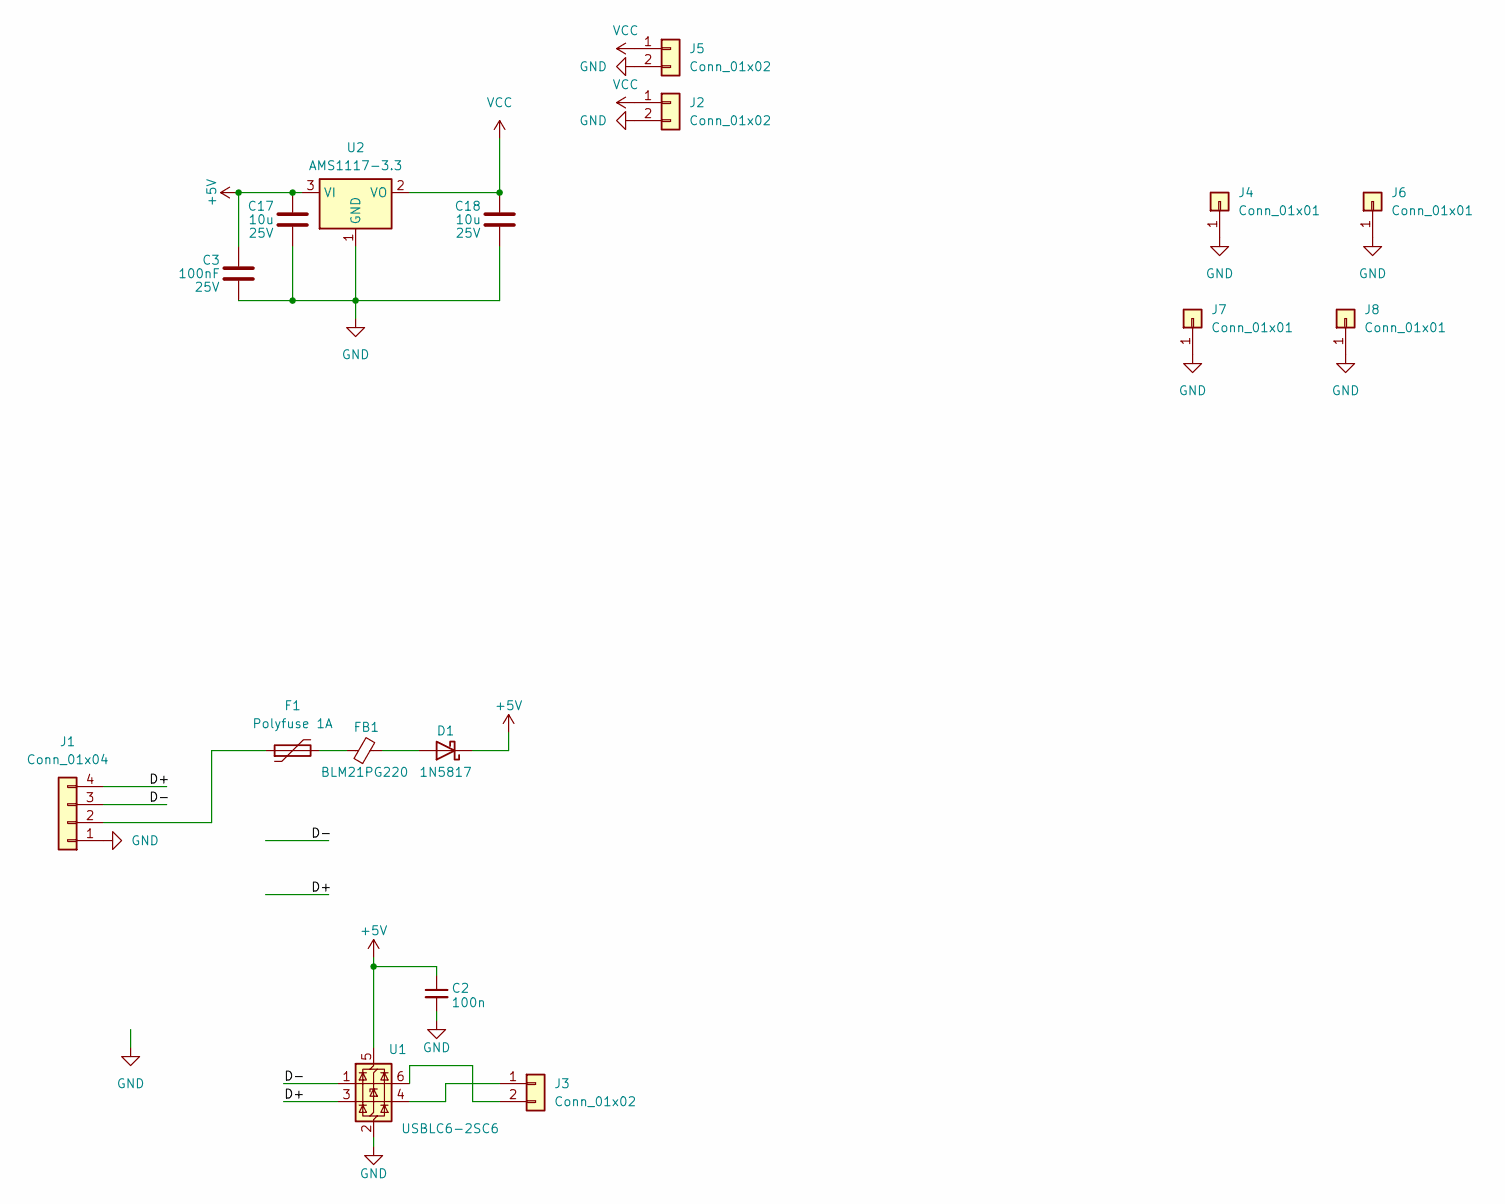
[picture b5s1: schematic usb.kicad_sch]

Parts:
C2: 100n; C_0402_1005Metric_Pad0.74x0.62mm_HandSolder
C3: 100nF; C_0603_1608Metric; Voltage 25V; LCSC Part # C96446
C17, C18: 10u; C_0603_1608Metric; Voltage 25V; LCSC Part # C96446
D1: 1N5817; SOD2613X110N; LCSC C2828424
F1: Polyfuse 1A; Fuse_1206_3216Metric
FB1: BLM21PG220; L_0805_2012Metric
J1: Conn_01x04; PinHeader_1x04_P2.54mm_Vertical
J2, J5: Conn_01x02; S2BZRLFSN; LCSC C157930
J3: Conn_01x02; JST_SHL_SM02B-SHLS-TF_1x02-1MP_P1.00mm_Horizontal; LCSC C160402
J4, J6, J7, J8: Conn_01x01; PinHeader_1x01_P1.00mm_Vertical
U1: USBLC6-2SC6; SOT-23-6
U2: AMS1117-3.3; SOT-89-3; LCSC Part # C7473143

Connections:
+5V: C2.1, C3.1, C17.1, D1.1 (K), U1.5 (VBUS), U2.3 (VI)
/D+: J1.4, U1.3 (I/O2)
/D-: J1.3, U1.1 (I/O1)
GND: C2.2, C3.2, C17.2, C18.2, J1.1, J2.2, J4.1, J5.2, J6.1, J7.1, J8.1, U1.2 (GND), U2.1 (GND)
unnamed: D1.2 (A), FB1.2
unnamed: F1.2, FB1.1
unnamed: F1.1, J1.2
unnamed: J3.1, U1.4 (I/O2)
unnamed: J3.2, U1.6 (I/O1)
VCC: C18.1, J2.1, J5.1, U2.2 (VO)

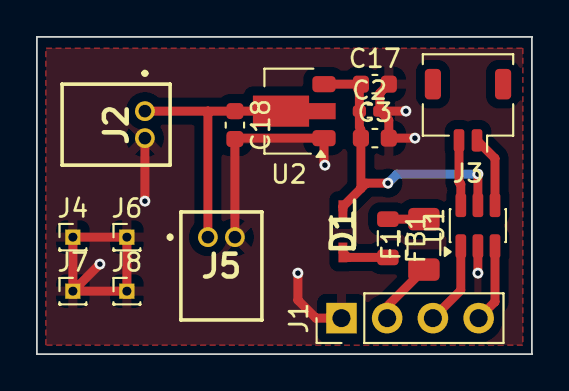
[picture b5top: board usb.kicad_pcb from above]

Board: 2 copper layers, 27.5 x 17.6 mm, 17 parts (0 on the bottom side), 10 nets.

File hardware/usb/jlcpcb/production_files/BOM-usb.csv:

Comment,Designator,Footprint,LCSC,Quantity
100n,C2,C_0402_1005Metric_Pad0.74x0.62mm_HandSolder,C1525,1
100nF,C3,C_0603_1608Metric,C14663,1
10u,"C17,C18",C_0603_1608Metric,C96446,2
1N5817,D1,SOD2613X110N,C2828424,1
AMS1117-3.3,U2,SOT-89-3,C7473143,1
BLM21PG220,FB1,L_0805_2012Metric,C88993,1
Conn_01x02,"J2,J5",S2BZRLFSN,C157930,2
Conn_01x02,J3,JST_SHL_SM02B-SHLS-TF_1x02-1MP_P1.00mm_Horizontal,C160402,1
Polyfuse 1A,F1,Fuse_1206_3216Metric,C1020,1
USBLC6-2SC6,U1,SOT-23-6,C2687116,1
Conn_01x04,J1,PinHeader_1x04_P2.54mm_Vertical,,1
Conn_01x01,J8,PinHeader_1x01_P1.00mm_Vertical,,1
Conn_01x01,J7,PinHeader_1x01_P1.00mm_Vertical,,1
Conn_01x01,J6,PinHeader_1x01_P1.00mm_Vertical,,1
Conn_01x01,J4,PinHeader_1x01_P1.00mm_Vertical,,1
